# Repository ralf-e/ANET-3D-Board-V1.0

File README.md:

## ANET-3D-Board-V1.0

Only a traced circuit diagram of the ANET A6 / A8 board, hopefully error free.

For information purposes....

- Anet 3D Printer Board V1.0 Schematic (Anet A6 / A8)
- Anet 3D Printer LCD12864 Graphics LCD Board Schematic (Anet A6 / A8)
- Anet 3D Printer LCD2004 Keypad LCD Board Schematic (draft) (ANET A8)
- Mosfet Board Schematic

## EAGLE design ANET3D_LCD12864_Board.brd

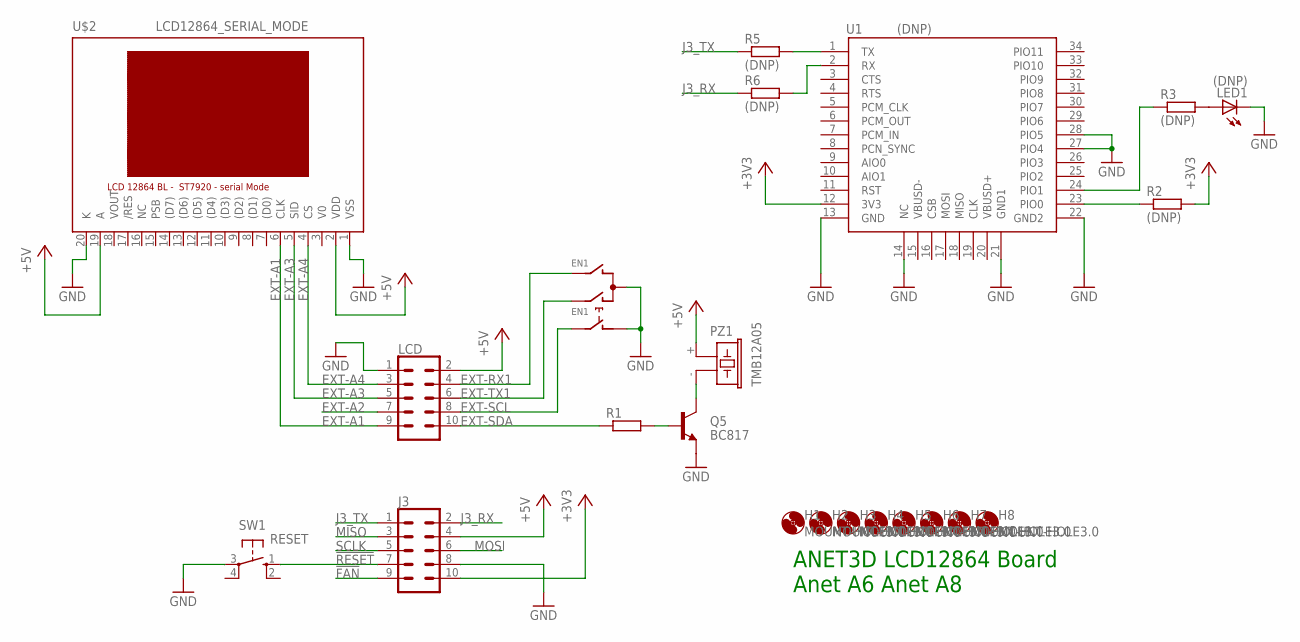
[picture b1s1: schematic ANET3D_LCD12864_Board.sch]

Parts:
EN1: EC12E_SW; ALPS_EC12E_SW
H1, H2, H3, H4, H5, H6, H7, H8: MOUNT-HOLE3.0; 3,0
J3: CONN_05X2SHD_SMD; 2X5-SHROUDED_SMD
LCD: CONN_05X2SHD_SMD; 2X5-SHROUDED_SMD
LED1: (DNP); CHIPLED_0805
PZ1: TMB12A05; F/CM12P
Q5: BC817; SOT23-BEC
R1: R-EU_R0805; R0805
R2, R3, R5, R6: (DNP); R0805
SW1: RESET; B3F-40XX
U1: (DNP); BLUETOOTH_SMD
U$2: LCD12864_SERIAL_MODE; LCD12864

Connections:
!FAN: J3.9
!RESET: J3.7, SW1.1 (S)
+3V3: J3.10, R2.2, U1.12 (3V3)
+5V: J3.4, LCD.2, PZ1.+ (1), U$2.2 (VDD), U$2.19 (A)
EXT-A1: LCD.9, U$2.6 (CLK)
EXT-A2: LCD.7
EXT-A3: LCD.5, U$2.5 (SID)
EXT-A4: LCD.3, U$2.4 (CS)
EXT-RX1: EN1.B, LCD.4
EXT-SCL: EN1.E (2), LCD.8
EXT-SDA: LCD.10, R1.1
EXT-TX1: EN1.A, LCD.6
GND: EN1.C, EN1.D (1), J3.8, LCD.1, LED1.C, Q5.E, SW1.3, U1.13 (GND), U1.14 (NC), U1.21 (GND1), U1.22 (GND2), U1.27 (PIO4), U1.28 (PIO5), U$2.1 (VSS), U$2.20 (K)
J3_RX: J3.2, R6.1
J3_TX: J3.1, R5.1
MISO: J3.3
MOSI: J3.6
unnamed: Q5.B, R1.2
unnamed: R3.1, U1.24 (PIO1)
unnamed: PZ1.- (2), Q5.C
unnamed: LED1.A, R3.2
unnamed: R5.2, U1.1 (TX)
unnamed: R6.2, U1.2 (RX)
unnamed: R2.1, U1.23 (PIO0)
SCLK: J3.5

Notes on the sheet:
ANET3D LCD12864 Board Anet A6 Anet A8

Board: 2 copper layers, 22 parts (10 on the bottom side), 20 nets, no tracks yet.

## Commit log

2017-06-16 added .pdf .png
2017-06-16 readme changed
2017-06-16 Arduino Pin definition added (for NAET 3D Board LED D1 (LED_BUILTIN))
2017-06-18 ANET A8 Keypad LCD added
2017-06-18 LCD2004 keypad resistor values
2017-06-19 remove .brd
2017-06-25 added ANET ISP-Adapter
2017-09-09 value R31 corrected
2017-12-19 Anet3d LCD2004 Resistor values corrected
2017-12-20 R/W corrected

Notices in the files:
parts and their libraries:
SparkFun-Connectors: Licensing: Creative Commons ShareAlike 4.0 International - https://creativecommons.org/licenses/by-sa/4.0
